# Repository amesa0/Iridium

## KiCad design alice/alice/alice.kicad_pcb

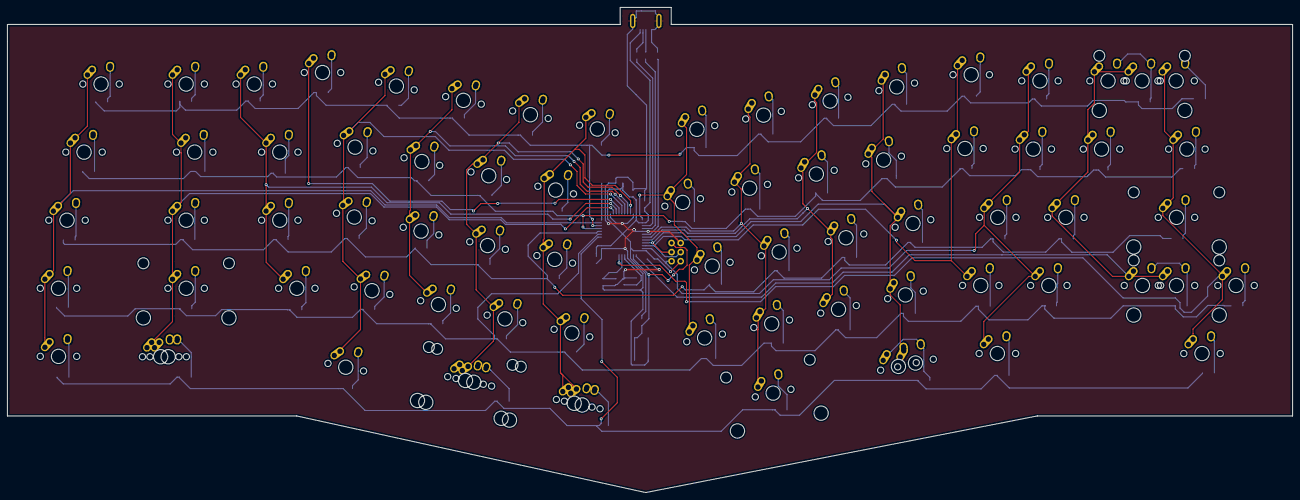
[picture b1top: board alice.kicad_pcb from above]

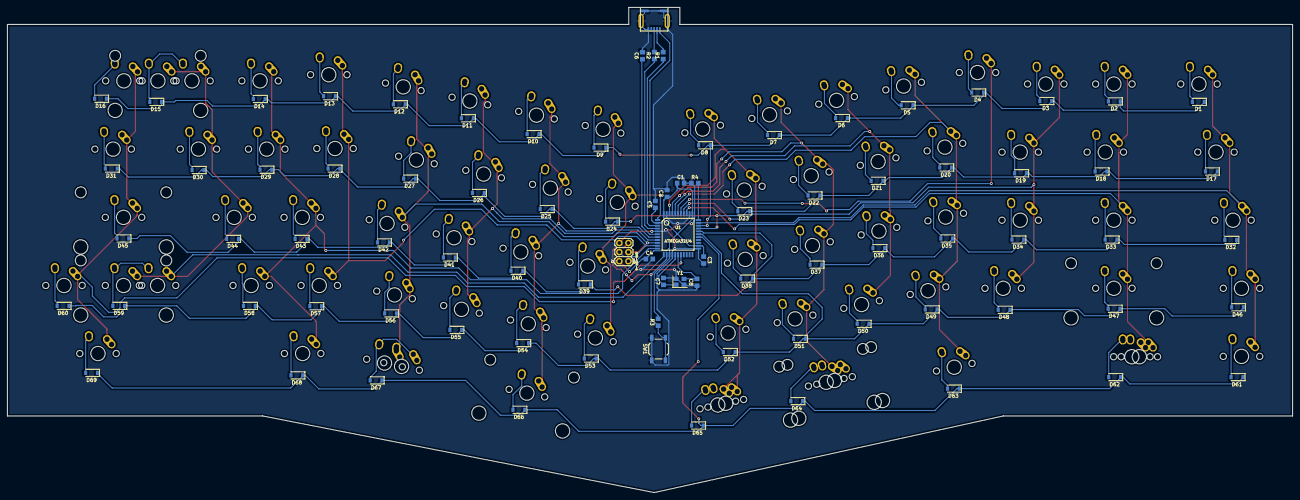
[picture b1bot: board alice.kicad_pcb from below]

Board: 2 copper layers, 358.6 x 135.4 mm, 161 parts (86 on the bottom side), 101 nets.

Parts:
C1, C2, C3, C4, C5: 0.1u; C_0805_2012Metric_Pad1.29x1.40mm_HandSolder
C6: 1u; C_0805_2012Metric_Pad1.29x1.40mm_HandSolder
C7, C8: 22p; C_0805_2012Metric_Pad1.29x1.40mm_HandSolder
D1, D2, D3, D4, D5, D6, D7, D8, D9, D10, D11, D12, D13, D14, D15, D16, D17, D18, D19, D20, D21, D22, D23, D24, D25, D26, D27, D28, D29, D30, D31, D32, D33, D34, D35, D36, D37, D38, D39, D40, D41, D42, D43, D44, D45, D46, D47, D48, D49, D50, D51, D52, D53, D54, D55, D56, D57, D58, D59, D60, D61, D62, D63, D64, D65, D66, D67, D68, D69: D; D_SOD-123
J1: USB_mini_micro_B; USB_miniB_hirose_5S8
J2: AVR-ISP-6; 2X3
K1, K2, K3, K4, K5, K6, K7, K8, K9, K10, K11, K12, K13, K14, K15, K16, K18, K20, K21, K22, K23, K24, K25, K26, K27, K28, K29, K30, K31, K33, K35, K36, K37, K38, K39, K40, K41, K42, K43, K44, K45, K47, K49, K50, K51, K52, K53, K54, K55, K56, K57, K58, K59, K61, K63, K65, K66: KEYSW; MX-1U-NoLED
K17, K69: KEYSW; MX-2U-NoLED
K19, K32, K67, K67#2, K68, K72, K73, K74: KEYSW; MX-1.5U-NoLED
K34, K62: KEYSW; MX-1.75U-NoLED
K46, K48, K64: KEYSW; MX-2.25U-NoLED
K60, K71: KEYSW; MX-2.75U-NoLED
K70: KEYSW; MX-1.25U-NoLED
R1, R2: 22; R_0805_2012Metric_Pad1.29x1.40mm_HandSolder
R3, R4: 10k; R_0805_2012Metric_Pad1.29x1.40mm_HandSolder
SW1: SW_PUSH; SW_SPST_TL3342
U1: ATMEGA32U4; QFP44_reflow
Y1: Crystal_GND24; Crystal_SMD_SeikoEpson_FA238-4Pin_3.2x2.5mm

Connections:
GND: C1.2, C2.2, C3.2, C4.2, C5.2, C6.2, C7.2, C8.1, J1.5, J1.6, J2.6, R4.1, SW1.1, U1.5, U1.15, U1.23, U1.35, U1.43, Y1.2, Y1.4
unnamed: C6.1, U1.6
unnamed: C7.1, U1.16, Y1.1
unnamed: C8.2, U1.17, Y1.3
unnamed: D1.2, K1.2
unnamed: D2.2, K2.2
unnamed: D3.2, K3.2
unnamed: D4.2, K4.2
unnamed: D5.2, K5.2
unnamed: D6.2, K6.2
unnamed: D7.2, K7.2
unnamed: D8.2, K8.2
unnamed: D9.2, K9.2
unnamed: D10.2, K10.2
unnamed: D11.2, K11.2
unnamed: D12.2, K12.2
unnamed: D13.2, K13.2
unnamed: D14.2, K14.2
unnamed: D15.2, K15.2, K17.2
unnamed: D16.2, K16.2
unnamed: D17.2, K18.2
unnamed: D18.2, K19.2
unnamed: D19.2, K20.2
unnamed: D20.2, K21.2
unnamed: D21.2, K22.2
unnamed: D22.2, K23.2
unnamed: D23.2, K24.2
unnamed: D24.2, K25.2
unnamed: D25.2, K26.2
unnamed: D26.2, K27.2
unnamed: D27.2, K28.2
unnamed: D28.2, K29.2
unnamed: D29.2, K30.2
unnamed: D30.2, K31.2
unnamed: D31.2, K32.2
unnamed: D32.2, K33.2
unnamed: D33.2, K34.2
unnamed: D34.2, K35.2
unnamed: D35.2, K36.2
unnamed: D36.2, K37.2
unnamed: D37.2, K38.2
unnamed: D38.2, K39.2
unnamed: D39.2, K40.2
unnamed: D40.2, K41.2
unnamed: D41.2, K42.2
unnamed: D42.2, K43.2
unnamed: D43.2, K44.2
unnamed: D44.2, K45.2
unnamed: D45.2, K46.2
unnamed: D46.2, K47.2
unnamed: D47.2, K48.2
unnamed: D48.2, K49.2
unnamed: D49.2, K50.2
unnamed: D50.2, K51.2
unnamed: D51.2, K52.2
unnamed: D52.2, K53.2
unnamed: D53.2, K54.2
unnamed: D54.2, K55.2
unnamed: D55.2, K56.2
unnamed: D56.2, K57.2
unnamed: D57.2, K58.2
unnamed: D58.2, K59.2
unnamed: D59.2, K60.2, K62.2
unnamed: D60.2, K61.2
unnamed: D61.2, K66.2
unnamed: D62.2, K67.2, K67#2.2
unnamed: D63.2, K68.2
unnamed: D64.2, K64.2, K69.2
unnamed: D65.2, K65.2, K70.2
unnamed: D66.2, K71.2
unnamed: D67.2, K63.1, K72.2
unnamed: D68.2, K73.2
unnamed: D69.2, K74.2
unnamed: J1.2, R1.2
unnamed: J1.3, R2.2
unnamed: J2.5, R3.1, SW1.2, U1.13
unnamed: R1.1, U1.3
unnamed: R2.1, U1.4
unnamed: R4.2, U1.33
VCC: C1.1, C2.1, C3.1, C4.1, C5.1, J1.1, J2.2, R3.2, U1.2, U1.14, U1.24, U1.34, U1.44
col0: K1.1, K18.1, K33.1, K47.1, K66.1, U1.32
col1: K2.1, K19.1, K34.1, K48.1, K67.1, U1.36
col2: K3.1, K20.1, K35.1, K49.1, U1.37
col3: K4.1, U1.38
col4: K5.1, K21.1, K36.1, K50.1, K68.1, U1.39
col5: K6.1, K22.1, K37.1, K51.1, U1.40
col6: K7.1, K23.1, K38.1, K52.1, K64.1, K69.1, U1.41
col7: K8.1, K24.1, K39.1, K53.1, K65.1, K70.1, U1.42
col8: K9.1, K25.1, K40.1, K54.1, U1.1
col9: K10.1, K26.1, K41.1, K55.1, K71.1, U1.7
col10: K11.1, K27.1, K42.1, K56.1, U1.8
col11: J2.3, K12.1, K28.1, K43.1, K57.1, K63.2, K72.1, U1.9
col12: J2.4, K13.1, K29.1, K58.1, U1.10
col13: J2.1, K14.1, K30.1, K44.1, K59.1, K73.1, U1.11
col14: K15.1, K17.1, K31.1, K45.1, K60.1, K62.1, U1.12
col15: K16.1, K32.1, K46.1, K61.1, K74.1, U1.18
row0: D1.1, D2.1, D3.1, D4.1, D5.1, D6.1, D7.1, D8.1, D9.1, D10.1, D11.1, D12.1, D13.1, D14.1, D15.1, D16.1, U1.31
row1: D17.1, D18.1, D19.1, D20.1, D21.1, D22.1, D23.1, D24.1, D25.1, D26.1, D27.1, D28.1, D29.1, D30.1, D31.1, U1.30
row2: D32.1, D33.1, D34.1, D35.1, D36.1, D37.1, D38.1, D39.1, D40.1, D41.1, D42.1, D43.1, D44.1, D45.1, U1.29
row3: D46.1, D47.1, D48.1, D49.1, D50.1, D51.1, D52.1, D53.1, D54.1, D55.1, D56.1, D57.1, D58.1, D59.1, D60.1, U1.28
row4: D61.1, D62.1, D63.1, D64.1, D65.1, D66.1, D67.1, D68.1, D69.1, U1.27

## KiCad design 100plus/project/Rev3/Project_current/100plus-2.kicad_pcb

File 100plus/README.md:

## TODO:
1. ~~Move usb to centre~~ Decided against it due to it visually looking odd when board is full  
2. ~~Move Controller to accomodate ^~~
3. ~~Add slots to left macros~~ Completed
4. Clean routing

## Ideas:
1. ~~Offboard controller compatibility for numpad incase of detachment~~ 
2. BT module, I2C pins free

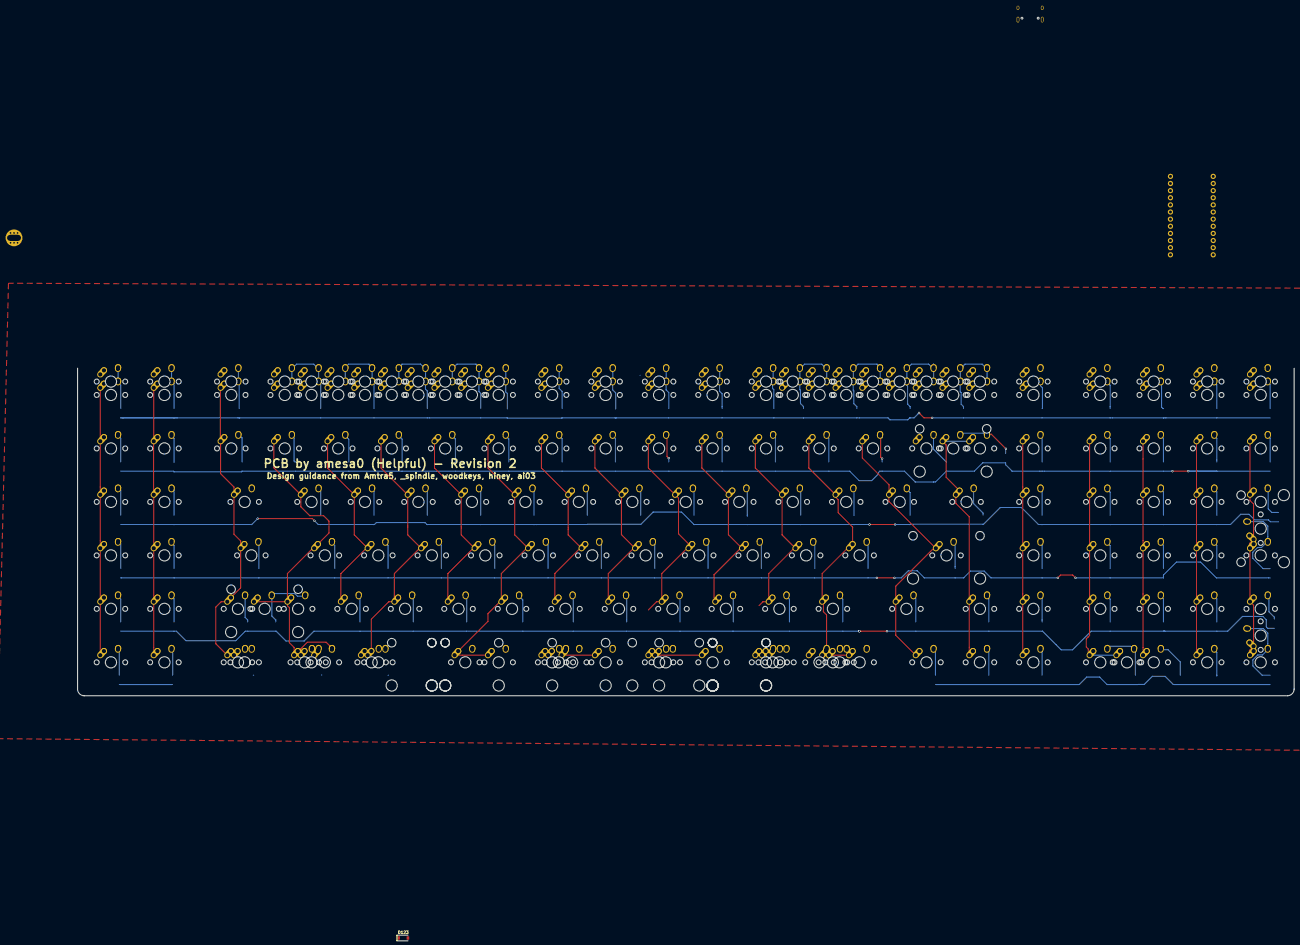
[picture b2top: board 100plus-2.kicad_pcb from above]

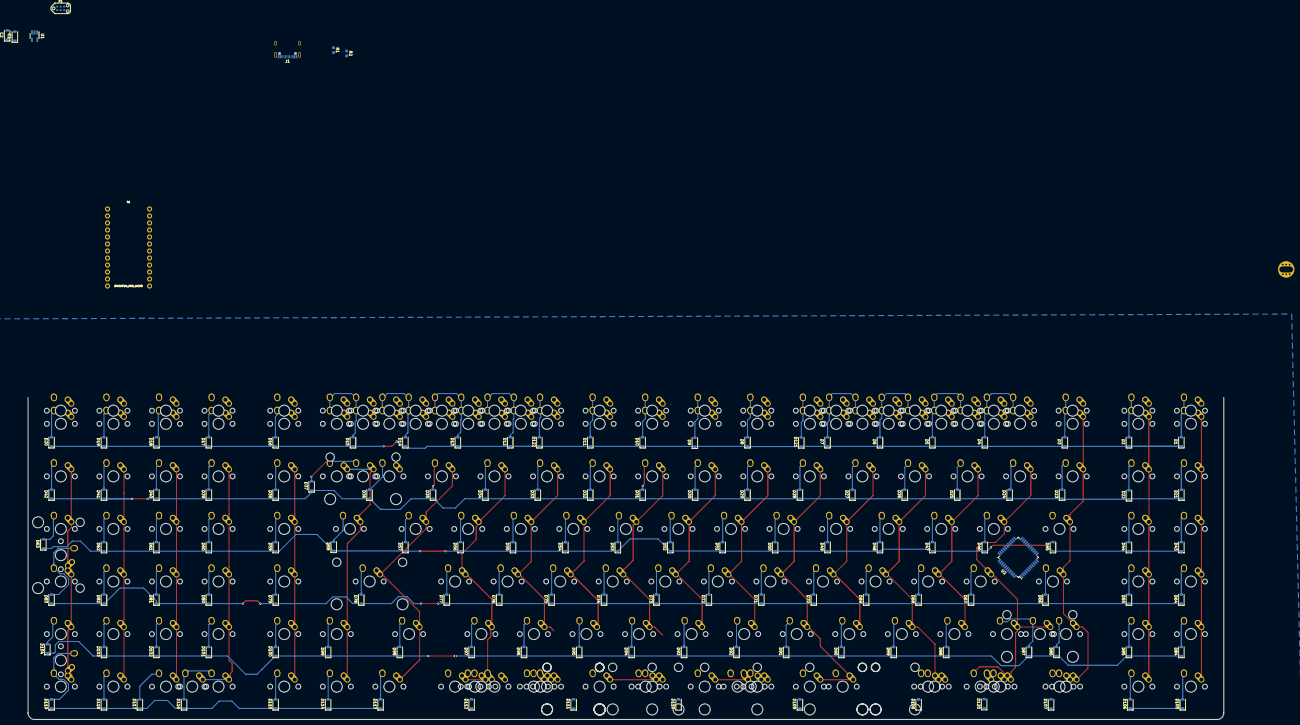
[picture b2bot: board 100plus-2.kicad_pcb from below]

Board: 2 copper layers, 433.4 x 116.7 mm, 314 parts (131 on the bottom side), 160 nets.

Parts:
B1: SPARKFUN_PRO_MICRO
C1: 10uf; D_SOD-123
C2: 0.4uf; D_SOD-123
D1, D2, D3, D4, D5, D6, D7, D8, D9, D10, D11, D12, D13, D14, D15, D16, D17, D18, D19, D20, D21, D22, D23, D24, D25, D26, D27, D28, D29, D30, D31, D32, D33, D34, D35, D36, D37, D38, D39, D40, D41, D42, D43, D44, D45, D46, D47, D48, D49, D50, D51, D52, D53, D54, D55, D56, D57, D58, D59, D60, D61, D62, D63, D64, D65, D66, D67, D68, D69, D70, D71, D72, D73, D74, D75, D76, D77, D78, D79, D80, D81, D82, D83, D84, D85, D86, D87, D88, D89, D90, D91, D92, D93, D94, D95, D96, D97, D98, D99, D100, D101, D102, D103, D104, D105, D106, D107, D108, D109, D110, D111, D112, D113, D114, D115, D116, D117, D118, D119, D120, D121, D122, D123: D; D_SOD-123
J1: USB_Type_C_2.0_Receptacle; USB_TypeC_U31F-24SNA0201
K1, K2, K3, K4, K5, K6, K7, K8, K9, K10, K11, K12, K13, K14, K15, K16, K17, K18, K19, K20, K21, K22, K23, K24, K25, K26, K27, K28, K29, K30, K31, K32, K33, K34, K35, K36, K37, K38, K39, K40, K41, K42, K43, K45, K46, K48, K49, K50, K51, K52, K53, K54, K55, K56, K57, K58, K59, K61, K62, K63, K64, K65, K67, K68, K70, K71, K72, K73, K74, K75, K76, K77, K78, K79, K80, K82, K83, K84, K85, K86, K87, K88, K90, K91, K92, K93, K94, K95, K96, K97, K98, K99, K100, K102, K103, K104, K105, K106, K107, K109, K111, K112, K117, K119, K120, K121, K122, K123, K124, K125, K128, K129, K130, K137, K138, K139, K143, K144, K145, K146, K147, K148, K157, K158, K159, K160, K165, K166, K167, K168, K169, K170, K171, K172, K173, K174, K175, K176, K177, K178, K179, K180, K181, K182, K183, K184, K185, K186, K187, K188, K189, K190: KEYSW; MX-1U-NoLED
K44, K66: KEYSW; MX-2U-NoLED
K47, K60, K113, K114, K118, K132, K134, K136: KEYSW; MX-1.5U-NoLED
K69, K101: KEYSW; MX-1.75U-NoLED
K81, K108, K155: KEYSW; MX-2.25U-NoLED
K89, K127, K131, K133, K152, K154, K156: KEYSW; MX-1.25U-NoLED
K110, K115, K116: KEYSW; MX-3U-NoLED
K126, K149: KEYSW; MX-7U-NoLED
K135: KEYSW; MX-2.75U-NoLED
K150: KEYSW; MX-6U-7UOverlay
K153: KEYSW; MX-6.25U-NoLED
P1: TC2030-IDC; TC2030-NL_SMALL
R1, R2: 5.1k; R_0603_1608Metric_Pad0.99x1.00mm_HandSolder
U1: MIC550X; SOT-23-5_HandSoldering
U2: ATXMEGA-A4U; TQFP-44_10x10mm_P0.8mm

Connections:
+5V: J1.A4, J1.B4, U1.1, U1.3
COL0: K1.1, K21.1, K45.1, K67.1, K87.1, K111.1, K169.1, U2.22
COL1: K2.1, K22.1, K46.1, K68.1, K88.1, K112.1, K170.1, U2.21
COL2: K3.1, K23.1, K47.1, K69.1, K89.1, K113.1, K131.1, K171.1, U2.20
COL3: K4.1, K24.1, K43.1, K48.1, K70.1, K90.1, K108.1, K130.1, K132.2, K152.1, K157.1, K172.1, U2.17
COL4: K5.1, K25.1, K49.1, K71.1, K91.1, K129.1, K158.1, K173.1, U2.16
COL5: K6.1, K26.1, K50.1, K72.1, K92.1, K114.1, K133.1, K137.1, K159.1, K174.1, U2.12
COL6: K7.1, K27.1, K51.1, K73.1, K93.1, K138.1, K160.1, K175.1, U2.13
COL7: K28.1, K52.1, K74.1, K94.1, K115.1, K147.1, K155.1, K176.1, U2.14
COL8: K8.1, K29.1, K53.1, K75.1, K95.1, K177.1, U2.15
COL9: K9.1, K30.1, K54.1, K76.1, K96.1, K178.1, U2.43
COL10: K10.1, K31.1, K55.1, K77.1, K97.1, K110.1, K116.1, K135.1, K179.1, U2.42
COL11: K11.1, K32.1, K56.1, K78.1, K98.1, K180.1, U2.41
COL12: K33.1, K57.1, K79.1, K99.1, K117.1, K127.1, K136.1, K148.1, K181.1, U2.40
COL13: K12.1, K34.1, K58.1, K80.1, K100.1, K118.1, K134.1, K139.2, K143.1, K154.1, K165.1, K182.1, U2.37
COL14: K13.1, K35.1, K59.1, K81.1, K101.1, K119.1, K144.1, K166.1, K183.1, U2.36
COL15: K14.1, K36.1, K145.1, K167.1, K184.1, U2.33
COL16: K15.1, K37.1, K44.1, K60.1, K102.1, K120.1, K146.1, K168.1, K185.1, U2.44
COL17: K16.1, K38.1, K61.1, K82.1, K103.1, K121.1, K186.1, U2.1
COL18: B1.14, K17.1, K39.1, K62.1, K83.1, K104.1, K122.1, K128.1, K187.1, U2.2
COL19: B1.13, K18.1, K40.1, K63.1, K84.1, K105.1, K123.1, K188.1, U2.3
COL20: B1.5, K19.1, K41.1, K64.1, K85.1, K106.1, K124.1, K189.1, U2.32
COL21: B1.6, K20.1, K42.1, K65.1, K66.1, K86.1, K107.1, K109.1, K125.1, K190.1, U2.25
GND: C1.2, C2.2, J1.A1, J1.B1, J1.S1, P1.6, R1.2, R2.2, U1.2, U2.8, U2.18, U2.30, U2.38
unnamed: D1.2, K1.2, K169.2
unnamed: D2.2, K2.2, K170.2
unnamed: D3.2, K3.2, K171.2
unnamed: D4.2, K4.2, K43.2, K157.2, K172.2
unnamed: D5.2, K5.2, K129.2, K158.2, K173.2
unnamed: D6.2, K6.2, K137.2, K159.2, K174.2
unnamed: D7.2, K7.2, K138.2, K160.2, K175.2
unnamed: D8.2, K8.2, K177.2
unnamed: D9.2, K9.2, K178.2
unnamed: D10.2, K10.2, K179.2
unnamed: D11.2, K11.2, K180.2
unnamed: D12.2, K12.2, K143.2, K165.2, K182.2
unnamed: D13.2, K13.2, K144.2, K166.2, K183.2
unnamed: D14.2, K14.2, K145.2, K167.2, K184.2
unnamed: D15.2, K15.2, K146.2, K168.2, K185.2
unnamed: D16.2, K16.2, K186.2
unnamed: D17.2, K17.2, K187.2
unnamed: D18.2, K18.2, K188.2
unnamed: D19.2, K19.2, K189.2
unnamed: D20.2, K20.2, K190.2
unnamed: D21.2, K21.2
unnamed: D22.2, K22.2
unnamed: D23.2, K23.2
unnamed: D24.2, K24.2
unnamed: D25.2, K25.2
unnamed: D26.2, K26.2
unnamed: D27.2, K27.2
unnamed: D28.2, K28.2
unnamed: D29.2, K29.2
unnamed: D30.2, K30.2
unnamed: D31.2, K31.2
unnamed: D32.2, K32.2
unnamed: D33.2, K33.2
unnamed: D34.2, K34.2
unnamed: D35.2, K35.2
unnamed: D36.2, K36.2
unnamed: D37.2, K37.2, K44.2
unnamed: D38.2, K38.2
unnamed: D39.2, K39.2
unnamed: D40.2, K40.2
unnamed: D41.2, K41.2
unnamed: D42.2, K42.2
unnamed: D43.2, K45.2
unnamed: D44.2, K46.2
unnamed: D45.2, K47.2
unnamed: D46.2, K48.2
unnamed: D47.2, K49.2
unnamed: D48.2, K50.2
unnamed: D49.2, K51.2
unnamed: D50.2, K52.2
unnamed: D51.2, K53.2
unnamed: D52.2, K54.2
unnamed: D53.2, K55.2
unnamed: D54.2, K56.2
unnamed: D55.2, K57.2
unnamed: D56.2, K58.2
unnamed: D57.2, K59.2
unnamed: D58.2, K60.2
unnamed: D59.2, K61.2
unnamed: D60.2, K62.2
unnamed: D61.2, K63.2
unnamed: D62.2, K64.2
unnamed: D63.2, K65.2
unnamed: D64.2, K67.2
unnamed: D65.2, K68.2
unnamed: D66.2, K69.2
unnamed: D67.2, K70.2
unnamed: D68.2, K71.2
unnamed: D69.2, K72.2
unnamed: D70.2, K73.2
unnamed: D71.2, K74.2
unnamed: D72.2, K75.2
unnamed: D73.2, K76.2
unnamed: D74.2, K77.2
unnamed: D75.2, K78.2
unnamed: D76.2, K79.2
unnamed: D77.2, K80.2
unnamed: D78.2, K81.2
unnamed: D79.2, K82.2
unnamed: D80.2, K83.2
unnamed: D81.2, K84.2
unnamed: D82.2, K85.2
unnamed: D83.2, K66.2, K86.2
unnamed: D84.2, K87.2
unnamed: D85.2, K88.2
unnamed: D86.2, K89.2
unnamed: D87.2, K90.2, K108.2
unnamed: D88.2, K91.2
unnamed: D89.2, K92.2
unnamed: D90.2, K93.2
unnamed: D91.2, K94.2
unnamed: D92.2, K95.2
unnamed: D93.2, K96.2
unnamed: D94.2, K97.2
unnamed: D95.2, K98.2
unnamed: D96.2, K99.2
unnamed: D97.2, K100.2
unnamed: D98.2, K101.2
unnamed: D99.2, K102.2
unnamed: D100.2, K103.2
unnamed: D101.2, K104.2
unnamed: D102.2, K105.2
unnamed: D103.2, K106.2
unnamed: D104.2, K107.2
unnamed: D105.2, K111.2
unnamed: D106.2, K112.2
unnamed: D107.2, K113.2, K131.2
unnamed: D108.2, K114.2, K133.2
unnamed: D109.2, K115.2, K155.2
unnamed: D110.2, K110.2, K116.2, K135.2
unnamed: D111.2, K117.2, K127.2, K136.2
unnamed: D112.2, K118.2, K134.2, K139.1, K154.2
unnamed: D113.2, K119.2
unnamed: D114.2, K120.2
unnamed: D115.2, K121.2
unnamed: D116.2, K122.2, K128.2
unnamed: D117.2, K123.2
unnamed: D118.2, K124.2
unnamed: D119.2, K109.2, K125.2
unnamed: D120.2, K130.2, K132.1, K152.2
unnamed: D121.2, K147.2, K176.2
unnamed: D122.2, K148.2, K181.2
unnamed: D123.2, K126.2, K149.2, K153.2, K156.2
unnamed: J1.A5, R2.1
unnamed: J1.A6, J1.B6, U2.27
unnamed: J1.A7, J1.B7, U2.26
unnamed: J1.B5, R1.1
PDI: P1.1, U2.34
ROW0: B1.7, D1.1, D2.1, D3.1, D4.1, D5.1, D6.1, D7.1, D8.1, D9.1, D10.1, D11.1, D12.1, D13.1, D14.1, D15.1, D16.1, D17.1, D18.1, D19.1, D20.1, D121.1, D122.1, U2.11
ROW1: B1.12, D21.1, D22.1, D23.1, D24.1, D25.1, D26.1, D27.1, D28.1, D29.1, D30.1, D31.1, D32.1, D33.1, D34.1, D35.1, D36.1, D37.1, D38.1, D39.1, D40.1, D41.1, D42.1, U2.4
ROW2: B1.11, D43.1, D44.1, D45.1, D46.1, D47.1, D48.1, D49.1, D50.1, D51.1, D52.1, D53.1, D54.1, D55.1, D56.1, D57.1, D58.1, D59.1, D60.1, D61.1, D62.1, D63.1, U2.5
ROW3: B1.10, D64.1, D65.1, D66.1, D67.1, D68.1, D69.1, D70.1, D71.1, D72.1, D73.1, D74.1, D75.1, D76.1, D77.1, D78.1, D79.1, D80.1, D81.1, D82.1, D83.1, U2.6
ROW4: B1.9, D84.1, D85.1, D86.1, D87.1, D88.1, D89.1, D90.1, D91.1, D92.1, D93.1, D94.1, D95.1, D96.1, D97.1, D98.1, D99.1, D100.1, D101.1, D102.1, D103.1, D104.1, K126.1, K149.1, K153.1, U2.7
ROW5: B1.8, D105.1, D106.1, D107.1, D108.1, D109.1, D110.1, D111.1, D112.1, D113.1, D114.1, D115.1, D116.1, D117.1, D118.1, D119.1, D120.1, D123.1, U2.10
RST: P1.5, U2.35
VCC: C1.1, C2.1, P1.2, U1.5, U2.9, U2.19, U2.31, U2.39

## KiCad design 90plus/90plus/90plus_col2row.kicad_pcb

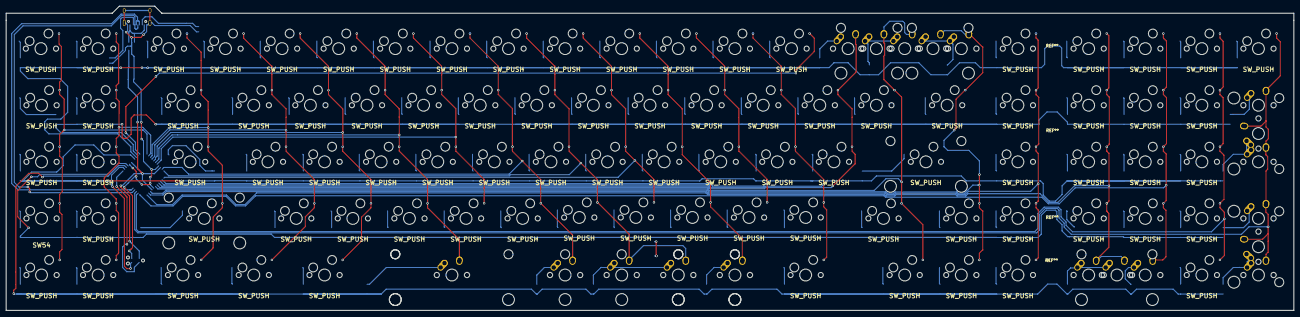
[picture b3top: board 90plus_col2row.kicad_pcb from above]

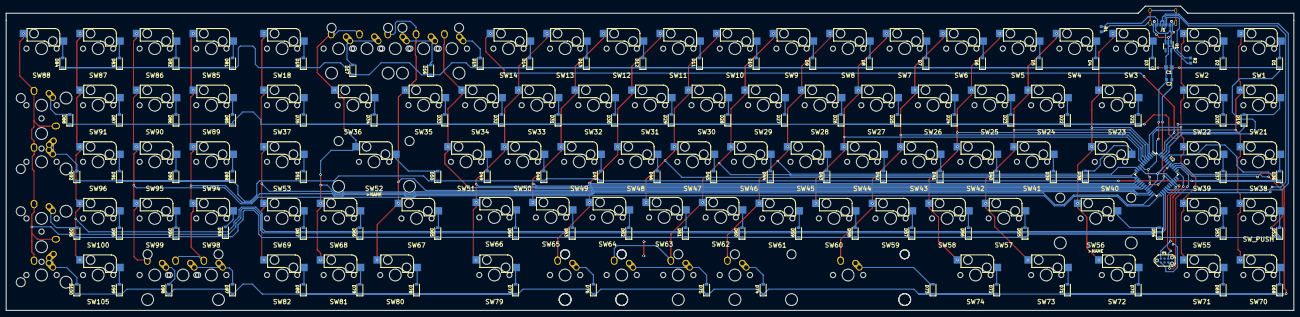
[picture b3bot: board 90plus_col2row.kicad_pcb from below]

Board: 2 copper layers, 433.4 x 102.4 mm, 217 parts (195 on the bottom side), 136 nets.

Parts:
>NAME: >VALUE; Mx_Stab_225
>NAME#2: >VALUE; Mx_Stab_225
C1: 10uf; C_0805_2012Metric_Pad1.29x1.40mm_HandSolder
C2: 0.4uf; C_0603_1608Metric_Pad0.99x1.00mm_HandSolder
D1, D2, D3, D4, D5, D6, D7, D8, D9, D10, D11, D12, D13, D14, D15, D16, D17, D18, D19, D20, D21, D22, D23, D24, D25, D26, D27, D28, D29, D30, D31, D32, D33, D34, D35, D36, D37, D38, D39, D40, D41, D42, D43, D44, D45, D46, D47, D48, D49, D50, D51, D52, D53, D54, D55, D56, D57, D58, D59, D60, D61, D62, D63, D64, D65, D66, D67, D68, D69, D70, D71, D72, D73, D74, D75, D76, D77, D78, D79, D80, D81, D82, D83, D84, D85, D86, D87, D88, D89, D90, D91, D92, D93, D94, D95, D96, D97, D98, D99, D100: D; D_SOD-123
J1: USB_Type_C_2.0_Receptacle; USB_TypeC_U31F-24SNA0201
P1: TC2030-IDC; TC2030-NL_SMALL
R1, R2: 5.1; R_0603_1608Metric_Pad0.99x1.00mm_HandSolder
SW1, SW2, SW3, SW4, SW5, SW6, SW7, SW8, SW9, SW10, SW11, SW12, SW13, SW14, SW18, SW21, SW22, SW23, SW24, SW25, SW26, SW27, SW28, SW29, SW30, SW31, SW32, SW33, SW34, SW35, SW36, SW37, SW38, SW39, SW40, SW41, SW42, SW43, SW44, SW45, SW46, SW47, SW48, SW49, SW50, SW51, SW52, SW53, SW54, SW55, SW56, SW57, SW58, SW59, SW60, SW61, SW62, SW63, SW64, SW65, SW66, SW67, SW68, SW69, SW70, SW71, SW72, SW73, SW74, SW79, SW80, SW81, SW82, SW85, SW86, SW87, SW88, SW89, SW90, SW91, SW94, SW95, SW96, SW98, SW99, SW100, SW105: SW_PUSH; Kailh_MX_Socket
SW15, SW19, SW20, SW78, SW92, SW97, SW101, SW103, SW104, SW106: SW_PUSH; MX-1U-NoLED
SW16, SW17, SW107: SW_PUSH; MX-2U-NoLED
SW75, SW77, SW84: SW_PUSH; MX-3U-NoLED
SW76: SW_PUSH; MX-7U-NoLED
SW83: SW_PUSH; MX-6U-7UOverlay
SW93, SW102: SW_PUSH; MX-2U-ReversedStabilizers-NoLED
U1: MIC550X; SOT-23-5_HandSoldering
U2: ATXMEGA-A4U-EPAD; TQFP-44_10x10mm_P0.8mm

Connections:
+5V: J1.A4, J1.B4, U1.1, U1.3
/COL0: SW1.2, SW21.2, SW38.2, SW54.2, SW70.2, U2.1
/COL1: SW2.2, SW22.2, SW39.2, SW55.2, SW71.2, U2.2
/COL2: SW3.2, SW23.2, SW40.2, SW56.2, SW72.2, U2.3
/COL3: SW4.2, SW24.2, SW41.2, SW57.2, SW73.2, U2.4
/COL4: SW5.2, SW25.2, SW42.2, SW58.2, SW74.2, U2.5
/COL5: SW6.2, SW26.2, SW43.2, SW59.2, SW75.2, U2.6
/COL6: SW7.2, SW27.2, SW44.2, SW60.2, U2.7
/COL7: SW8.2, SW28.2, SW45.2, SW61.2, SW76.2, U2.10
/COL8: SW9.2, SW29.2, SW46.2, SW62.2, SW77.2, SW84.2, U2.11
/COL9: SW10.2, SW30.2, SW47.2, SW63.2, U2.12
/COL10: SW11.2, SW31.2, SW48.2, SW64.2, SW78.2, U2.13
/COL11: SW12.2, SW32.2, SW49.2, SW65.2, U2.14
/COL12: SW13.2, SW33.2, SW50.2, SW66.2, SW79.2, U2.15
/COL13: SW14.2, U2.44
/COL14: SW15.2, SW34.2, SW51.2, U2.16
/COL15: SW16.2, SW20.2, SW35.2, SW67.2, SW80.2, U2.17
/COL16: SW17.2, SW19.2, SW36.2, SW52.2, SW68.2, SW81.2, U2.20
/COL17: SW18.2, SW37.2, SW53.2, SW69.2, SW82.2, U2.21
/COL18: SW85.2, SW89.2, SW94.2, SW98.2, SW103.2, SW107.2, U2.22
/COL19: SW86.2, SW90.2, SW95.2, SW99.2, SW104.2, U2.23
/COL20: SW87.2, SW91.2, SW96.2, SW100.2, SW105.2, U2.24
/COL21: SW88.2, SW92.2, SW93.2, SW97.2, SW101.2, SW102.2, SW106.2, U2.25
/PDI: P1.1, U2.34
/ROW0: D1.1, D2.1, D3.1, D4.1, D5.1, D6.1, D7.1, D8.1, D9.1, D10.1, D11.1, D12.1, D13.1, D14.1, D15.1, D16.1, D17.1, D18.1, D81.1, D82.1, D83.1, D84.1, U2.42
/ROW1: D19.1, D20.1, D21.1, D22.1, D23.1, D24.1, D25.1, D26.1, D27.1, D28.1, D29.1, D30.1, D31.1, D32.1, D33.1, D34.1, D35.1, D85.1, D86.1, D87.1, D88.1, U2.43
/ROW2: D36.1, D37.1, D38.1, D39.1, D40.1, D41.1, D42.1, D43.1, D44.1, D45.1, D46.1, D47.1, D48.1, D49.1, D50.1, D51.1, D89.1, D90.1, D91.1, D92.1, U2.41
/ROW3: D52.1, D53.1, D54.1, D55.1, D56.1, D57.1, D58.1, D59.1, D60.1, D61.1, D62.1, D63.1, D64.1, D65.1, D66.1, D67.1, D93.1, D94.1, D95.1, D96.1, U2.37
/ROW4: D68.1, D69.1, D70.1, D71.1, D72.1, D73.1, D74.1, D75.1, D76.1, D77.1, D78.1, D79.1, D80.1, D97.1, D98.1, D99.1, D100.1, U2.36
/RST: P1.5, U2.35
GND: C1.2, C2.2, J1.A1, J1.B1, J1.S1, P1.6, R1.2, R2.2, U1.2, U2.8, U2.18, U2.30, U2.38
unnamed: D1.2, SW1.1
unnamed: D2.2, SW2.1
unnamed: D3.2, SW3.1
unnamed: D4.2, SW4.1
unnamed: D5.2, SW5.1
unnamed: D6.2, SW6.1
unnamed: D7.2, SW7.1
unnamed: D8.2, SW8.1
unnamed: D9.2, SW9.1
unnamed: D10.2, SW10.1
unnamed: D11.2, SW11.1
unnamed: D12.2, SW12.1
unnamed: D13.2, SW13.1
unnamed: D14.2, SW14.1
unnamed: D15.2, SW15.1
unnamed: D16.2, SW16.1, SW20.1
unnamed: D17.2, SW17.1, SW19.1
unnamed: D18.2, SW18.1
unnamed: D19.2, SW21.1
unnamed: D20.2, SW22.1
unnamed: D21.2, SW23.1
unnamed: D22.2, SW24.1
unnamed: D23.2, SW25.1
unnamed: D24.2, SW26.1
unnamed: D25.2, SW27.1
unnamed: D26.2, SW28.1
unnamed: D27.2, SW29.1
unnamed: D28.2, SW30.1
unnamed: D29.2, SW31.1
unnamed: D30.2, SW32.1
unnamed: D31.2, SW33.1
unnamed: D32.2, SW34.1
unnamed: D33.2, SW35.1
unnamed: D34.2, SW36.1
unnamed: D35.2, SW37.1
unnamed: D36.2, SW38.1
unnamed: D37.2, SW39.1
unnamed: D38.2, SW40.1
unnamed: D39.2, SW41.1
unnamed: D40.2, SW42.1
unnamed: D41.2, SW43.1
unnamed: D42.2, SW44.1
unnamed: D43.2, SW45.1
unnamed: D44.2, SW46.1
unnamed: D45.2, SW47.1
unnamed: D46.2, SW48.1
unnamed: D47.2, SW49.1
unnamed: D48.2, SW50.1
unnamed: D49.2, SW51.1
unnamed: D50.2, SW52.1
unnamed: D51.2, SW53.1
unnamed: D52.2, SW54.1
unnamed: D53.2, SW55.1
unnamed: D54.2, SW56.1
unnamed: D55.2, SW57.1
unnamed: D56.2, SW58.1
unnamed: D57.2, SW59.1
unnamed: D58.2, SW60.1
unnamed: D59.2, SW61.1
unnamed: D60.2, SW62.1
unnamed: D61.2, SW63.1
unnamed: D62.2, SW64.1
unnamed: D63.2, SW65.1
unnamed: D64.2, SW66.1
unnamed: D65.2, SW67.1
unnamed: D66.2, SW68.1
unnamed: D67.2, SW69.1
unnamed: D68.2, SW70.1
unnamed: D69.2, SW71.1
unnamed: D70.2, SW72.1
unnamed: D71.2, SW73.1
unnamed: D72.2, SW74.1
unnamed: D73.2, SW75.1
unnamed: D74.2, SW76.1
unnamed: D75.2, SW77.1, SW84.1
unnamed: D76.2, SW78.1
unnamed: D77.2, SW79.1
unnamed: D78.2, SW80.1
unnamed: D79.2, SW81.1
unnamed: D80.2, SW82.1
unnamed: D81.2, SW85.1
unnamed: D82.2, SW86.1
unnamed: D83.2, SW87.1
unnamed: D84.2, SW88.1
unnamed: D85.2, SW89.1
unnamed: D86.2, SW90.1
unnamed: D87.2, SW91.1
unnamed: D88.2, SW92.1
unnamed: D89.2, SW94.1
unnamed: D90.2, SW95.1
unnamed: D91.2, SW96.1
unnamed: D92.2, SW93.1, SW97.1
unnamed: D93.2, SW98.1
unnamed: D94.2, SW99.1
unnamed: D95.2, SW100.1
unnamed: D96.2, SW101.1
unnamed: D97.2, SW103.1, SW107.1
unnamed: D98.2, SW104.1
unnamed: D99.2, SW105.1
unnamed: D100.2, SW102.1, SW106.1
unnamed: J1.A5, R2.1
unnamed: J1.A6, J1.B6, U2.27
unnamed: J1.A7, J1.B7, U2.26
unnamed: J1.B5, R1.1
VCC: C1.1, C2.1, P1.2, U1.5, U2.9, U2.19, U2.31, U2.39

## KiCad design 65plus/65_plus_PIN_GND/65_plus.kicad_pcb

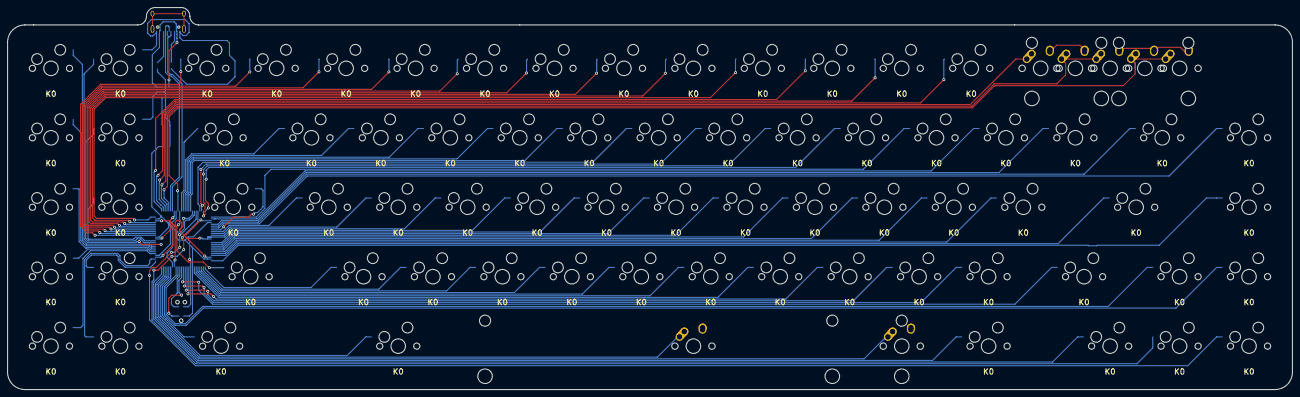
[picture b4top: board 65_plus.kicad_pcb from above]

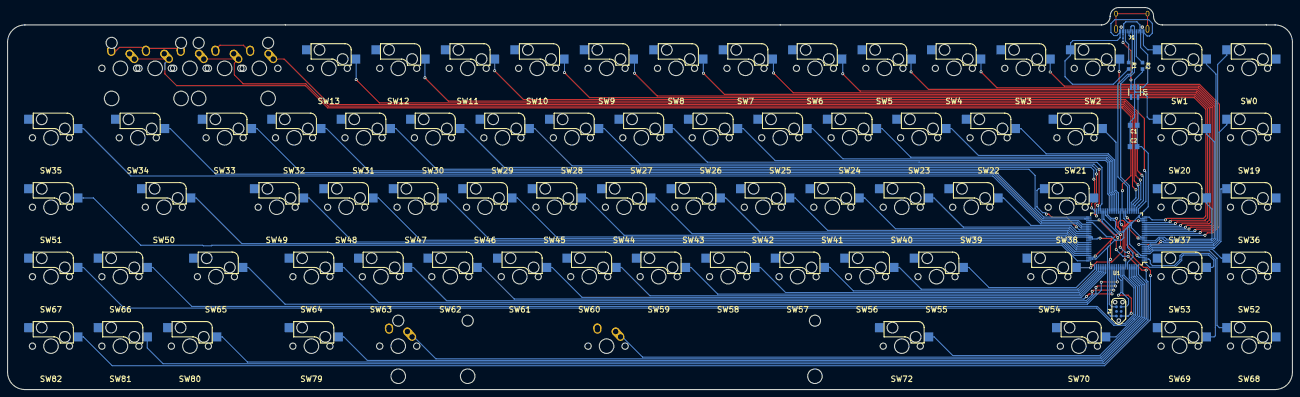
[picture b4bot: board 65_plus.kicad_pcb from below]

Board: 2 copper layers, 352.4 x 104.8 mm, 87 parts (79 on the bottom side), 85 nets.

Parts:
C1, C2: 10uf; C_0805_2012Metric_Pad1.29x1.40mm_HandSolder
J1: USB_Type_C_2.0_Receptacle; USB_TypeC_U31F-24SNA0201
P1: TC2030-IDC; TC2030-NL_SMALL
R1, R2: 5.1k; R_0603_1608Metric_Pad0.99x1.00mm_HandSolder
SW0, SW1, SW2, SW3, SW4, SW5, SW6, SW7, SW8, SW9, SW10, SW11, SW12, SW13, SW19, SW20, SW21, SW22, SW23, SW24, SW25, SW26, SW27, SW28, SW29, SW30, SW31, SW32, SW33, SW34, SW35, SW36, SW37, SW38, SW39, SW40, SW41, SW42, SW43, SW44, SW45, SW46, SW47, SW48, SW49, SW50, SW51, SW52, SW53, SW54, SW55, SW56, SW57, SW58, SW59, SW60, SW61, SW62, SW63, SW64, SW65, SW66, SW67, SW68, SW69, SW70, SW72, SW79, SW80, SW81, SW82: K0; Kailh_MX_Socket
SW14, SW15, SW17, SW78: K0; MX-1U-NoLED
SW14.5, SW16: K0; MX-2U-NoLED
SW74: K0; MX-7U-NoLED
SW75: K0; MX-6U-7UOverlay
U1: ATXMEGA128A1U-AU; TQFP-100_14x14mm_P0.5mm
U2: MIC550X; SOT-23-5_HandSoldering

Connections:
+5V: J1.A4, J1.B4, U2.1, U2.3
/KEY0: SW0.2, U1.9
/KEY1: SW1.1, U1.10
/KEY2: SW2.1, U1.15
/KEY3: SW3.1, U1.16
/KEY4: SW4.1, U1.17
/KEY5: SW5.1, U1.18
/KEY6: SW6.1, U1.19
/KEY7: SW7.1, U1.20
/KEY8: SW8.1, U1.21
/KEY9: SW9.1, U1.22
/KEY10: SW10.1, U1.25
/KEY11: SW11.1, U1.26
/KEY12: SW12.1, U1.27
/KEY13: SW13.1, U1.28
/KEY14: SW14.1, U1.29
/KEY14.5: SW14.5.1, SW15.1, U1.30
/KEY16: SW16.1, SW17.1, U1.35
/KEY19: SW19.2, U1.8
/KEY20: SW20.1, U1.11
/KEY21: SW21.1, U1.37
/KEY22: SW22.1, U1.38
/KEY23: SW23.1, U1.39
/KEY24: SW24.1, U1.40
/KEY25: SW25.1, U1.41
/KEY26: SW26.1, U1.42
/KEY27: SW27.1, U1.47
/KEY28: SW28.1, U1.48
/KEY29: SW29.1, U1.49
/KEY30: SW30.1, U1.50
/KEY31: SW31.1, U1.51
/KEY32: SW32.1, U1.52
/KEY33: SW33.1, U1.55
/KEY34: SW34.1, U1.56
/KEY35: SW35.1, U1.57
/KEY36: SW36.2, U1.7
/KEY37: SW37.1, U1.12
/KEY38: SW38.2, U1.58
/KEY39: SW39.1, U1.59
/KEY40: SW40.1, U1.60
/KEY41: SW41.1, U1.61
/KEY42: SW42.1, U1.62
/KEY43: SW43.1, U1.65
/KEY44: SW44.1, U1.66
/KEY45: SW45.1, U1.67
/KEY46: SW46.1, U1.68
/KEY47: SW47.1, U1.69
/KEY48: SW48.1, U1.70
/KEY49: SW49.1, U1.71
/KEY50: SW50.1, U1.72
/KEY51: SW51.1, U1.75
/KEY52: SW52.2, U1.6
/KEY53: SW53.1, U1.1
/KEY54: SW54.1, U1.36
/KEY55: SW55.1, U1.76
/KEY56: SW56.1, U1.77
/KEY57: SW57.1, U1.78
/KEY58: SW58.1, U1.79
/KEY59: SW59.1, U1.80
/KEY60: SW60.1, U1.81
/KEY61: SW61.1, U1.82
/KEY62: SW62.1, U1.85
/KEY63: SW63.1, U1.86
/KEY64: SW64.1, U1.87
/KEY65: SW65.1, U1.88
/KEY66: SW66.1, U1.91
/KEY67: SW67.1, U1.92
/KEY68: SW68.2, U1.5
/KEY69: SW69.1, U1.2
/KEY70: SW70.1, U1.95
/KEY72: SW72.1, U1.96
/KEY74: SW74.1, U1.97
/KEY78: SW78.1, U1.98
/KEY79: SW79.1, U1.99
/KEY80: SW80.1, U1.100
/KEY81: SW81.1, U1.46
/KEY82: SW82.1, U1.45
/PDI: P1.1, U1.89
/RST: P1.5, U1.90
GND: C1.2, C2.1, J1.A1, J1.B1, P1.6, R1.2, R2.2, SW0.1, SW1.2, SW2.2, SW3.2, SW4.2, SW5.2, SW6.2, SW7.2, SW8.2, SW9.2, SW10.2, SW11.2, SW12.2, SW13.2, SW14.2, SW14.5.2, SW15.2, SW16.2, SW17.2, SW19.1, SW20.2, SW21.2, SW22.2, SW23.2, SW24.2, SW25.2, SW26.2, SW27.2, SW28.2, SW29.2, SW30.2, SW31.2, SW32.2, SW33.2, SW34.2, SW35.2, SW36.1, SW37.2, SW38.1, SW39.2, SW40.2, SW41.2, SW42.2, SW43.2, SW44.2, SW45.2, SW46.2, SW47.2, SW48.2, SW49.2, SW50.2, SW51.2, SW52.1, SW53.2, SW54.2, SW55.2, SW56.2, SW57.2, SW58.2, SW59.2, SW60.2, SW61.2, SW62.2, SW63.2, SW64.2, SW65.2, SW66.2, SW67.2, SW68.1, SW69.2, SW70.2, SW72.2, SW74.2, SW78.2, SW79.2, SW80.2, SW81.2, SW82.2, U1.3, U1.13, U1.23, U1.33, U1.43, U1.53, U1.63, U1.73, U1.84, U1.93, U2.2
unnamed: J1.A5, R2.1
unnamed: J1.A6, J1.B6, U1.32
unnamed: J1.A7, J1.B7, U1.31
unnamed: J1.B5, R1.1
VCC: C1.1, C2.2, P1.2, U1.4, U1.14, U1.24, U1.34, U1.44, U1.54, U1.64, U1.74, U1.83, U1.94, U2.5
